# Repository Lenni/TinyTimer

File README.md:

# TinyTimer
Documentation for a Parachute Timer based on the Attiny85 Microcontroller

## Hardware

Eagle Files for etching a PCB to house the ATTiny. This will NOT include a list of parts to build the Timer yourself.

## Software

Arduino IDE Source Code to program the ATTiny. 
Please Note that you will need an Arduino or ISP to program the ATTiny. The EAGLE Files for a Demo Programminsg Shield are in the Hardware Folder.
 ## Disclaimer
 
 The Idea and the First Version of the Tiny Timer was made by Achim Oelkers (AchimO) on https://www.raketenmodellbau.org/forum?action=viewthread&threadid=801925&page=1 
 A friend and me only decided to optimize the Code for Usability and to provide Eagle files and schematics to make the recreation of this Timer as easy as possible.

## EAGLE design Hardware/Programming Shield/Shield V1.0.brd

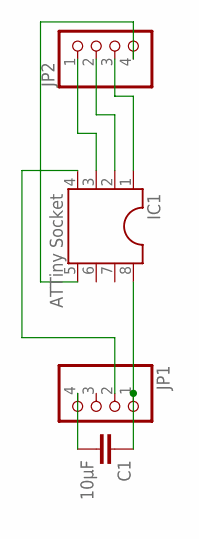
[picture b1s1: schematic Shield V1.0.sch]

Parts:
C1: 10µF; C2.5-3
IC1: ATTiny Socket; SOCKET-08
JP1, JP2: PINHD-1X4; 1X04

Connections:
unnamed: IC1.3, JP2.1
unnamed: IC1.2, JP2.2
unnamed: IC1.1, JP2.3
unnamed: IC1.5, JP2.4
unnamed: IC1.4, JP1.2
unnamed: C1.2, JP1.4
unnamed: C1.1, IC1.8, JP1.1

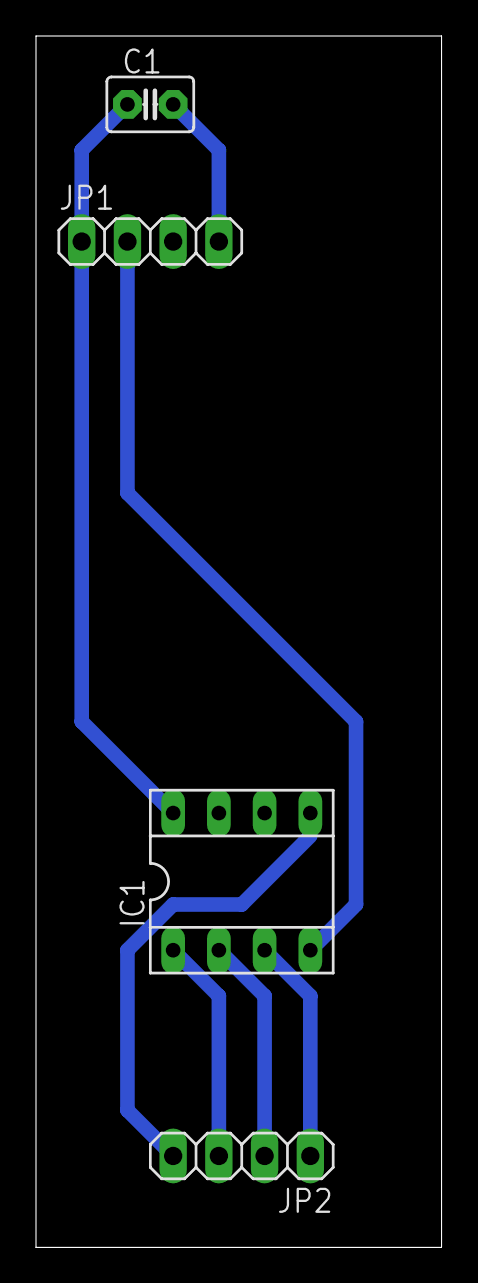
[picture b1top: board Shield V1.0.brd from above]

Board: 2 copper layers, 22.5 x 67.3 mm, 4 parts (0 on the bottom side), 7 nets.

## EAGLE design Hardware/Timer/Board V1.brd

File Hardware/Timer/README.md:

# TinyTimer
Documentation for a Parachute Timer based on the Attiny85 Microcontroller

## Hardware

Eagle Files for etching a PCB to house the ATTiny. This will NOT include a list of parts to build the Timer yourself.

The power supply for the Board can be any Power Source with a Voltage ranging from 3.7V to 5V. We used a small 100mAh Lithium-Polymer Battery to Power the Circuit and the Servo.

# Disclaimer
 
 The Idea and the First Version of the Tiny Timer was made by Achim Oelkers (AchimO) on http://raketenmodellbau.org 
 A friend an me only decided to optimize ther Code for Usability and to provide Eagle files and schematics to make the recreation of this Timer as easy as possible.

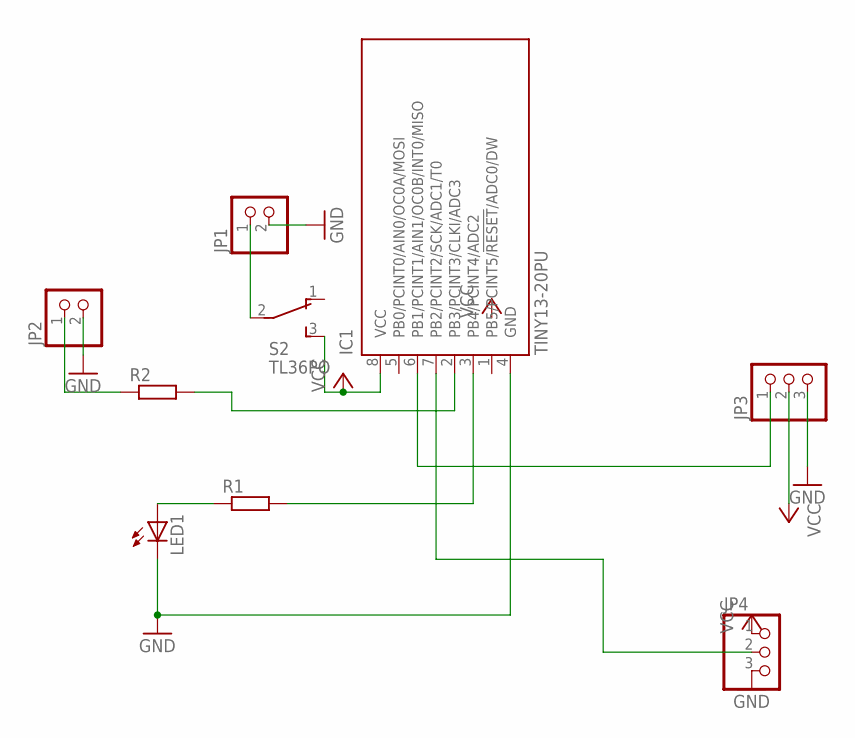
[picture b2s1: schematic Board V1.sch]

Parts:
IC1: TINY13-20PU; DIL08
JP1, JP2: PINHD-1X2; 1X02
JP3, JP4: PINHD-1X3; 1X03
LED1: LED5MM
R1, R2: R-EU_0204/7; 0204/7
S2: TL36PO; TL3XPO

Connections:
GND: IC1.4 (GND), JP1.2, JP2.2, JP3.3, JP4.3, LED1.K (C)
unnamed: JP2.1, R2.1
unnamed: IC1.2 (PB3/PCINT3/CLKI/ADC3), R2.2
unnamed: IC1.3 (PB4/PCINT4/ADC2), R1.2
unnamed: IC1.6 (PB1/PCINT1/AIN1/OC0B/INT0/MISO), JP3.1
unnamed: JP1.1, S2.2
unnamed: LED1.A, R1.1
unnamed: IC1.7 (PB2/PCINT2/SCK/ADC1/T0), JP4.2
VCC: IC1.8 (VCC), JP3.2, JP4.1, S2.3 (S)

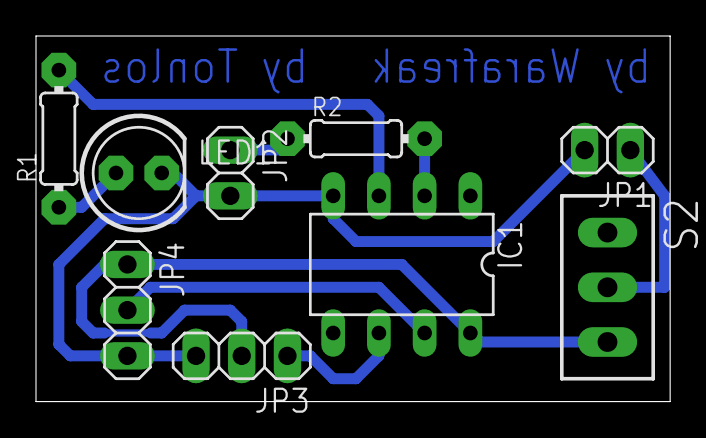
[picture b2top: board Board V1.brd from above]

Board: 2 copper layers, 35.2 x 20.3 mm, 9 parts (0 on the bottom side), 9 nets.

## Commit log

2017-06-04 Added Documentation and Hardware Files
2017-06-04 Update TinyTimer.ino
    Improved and field tested version
